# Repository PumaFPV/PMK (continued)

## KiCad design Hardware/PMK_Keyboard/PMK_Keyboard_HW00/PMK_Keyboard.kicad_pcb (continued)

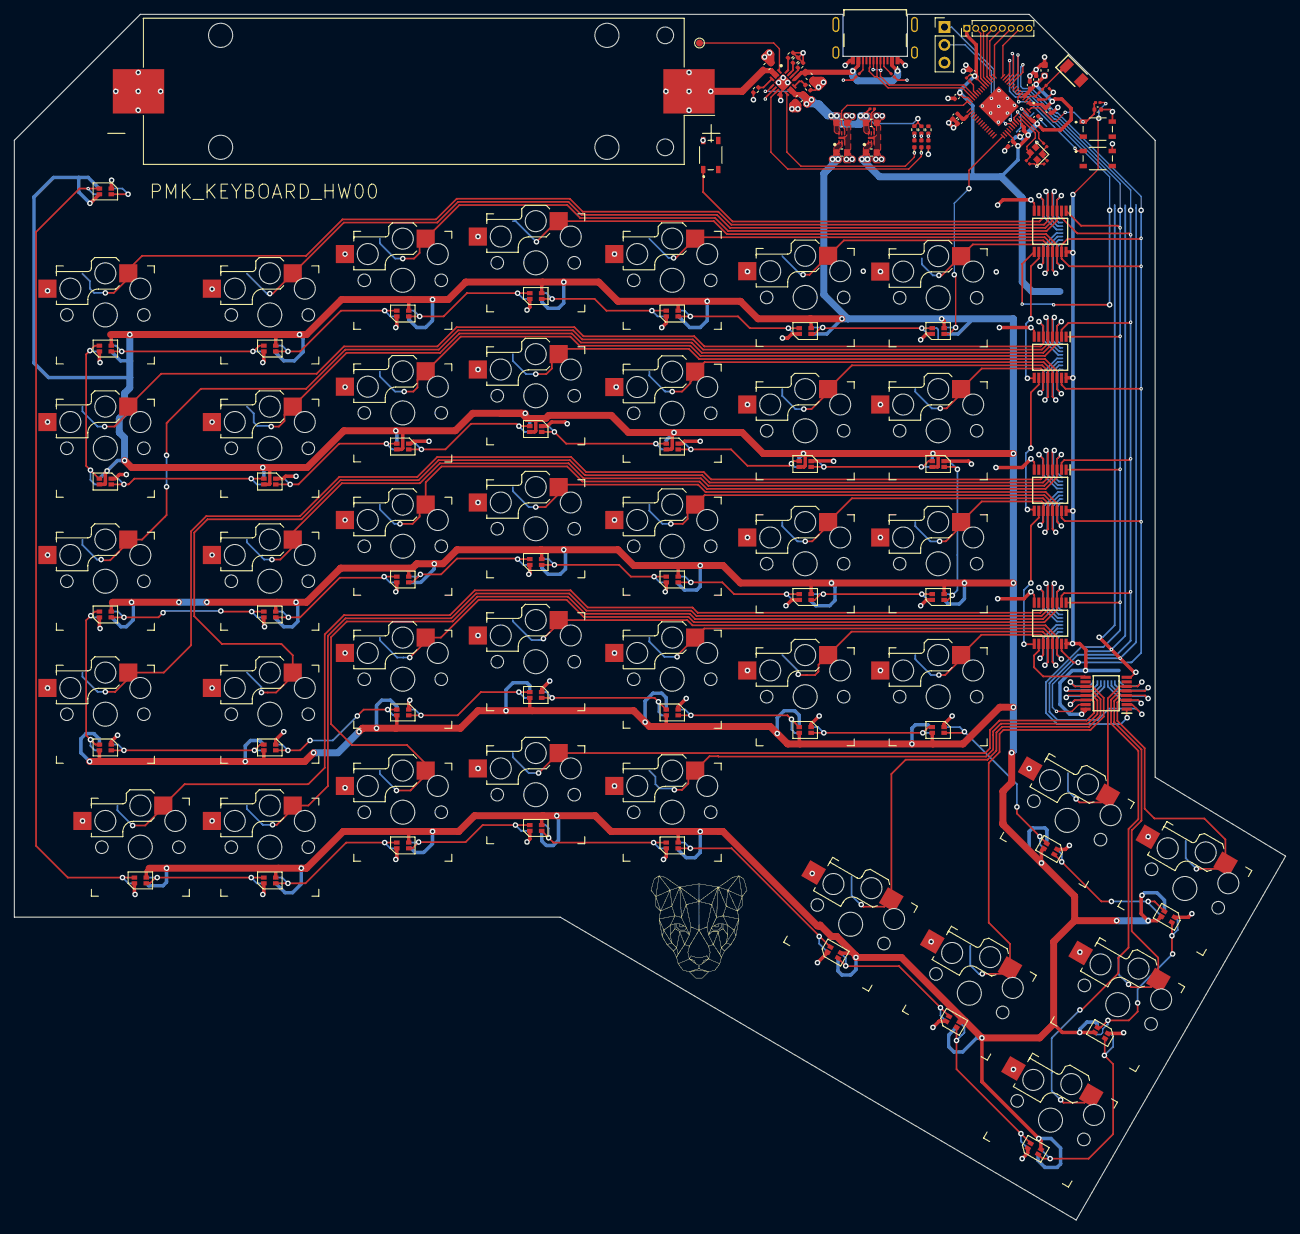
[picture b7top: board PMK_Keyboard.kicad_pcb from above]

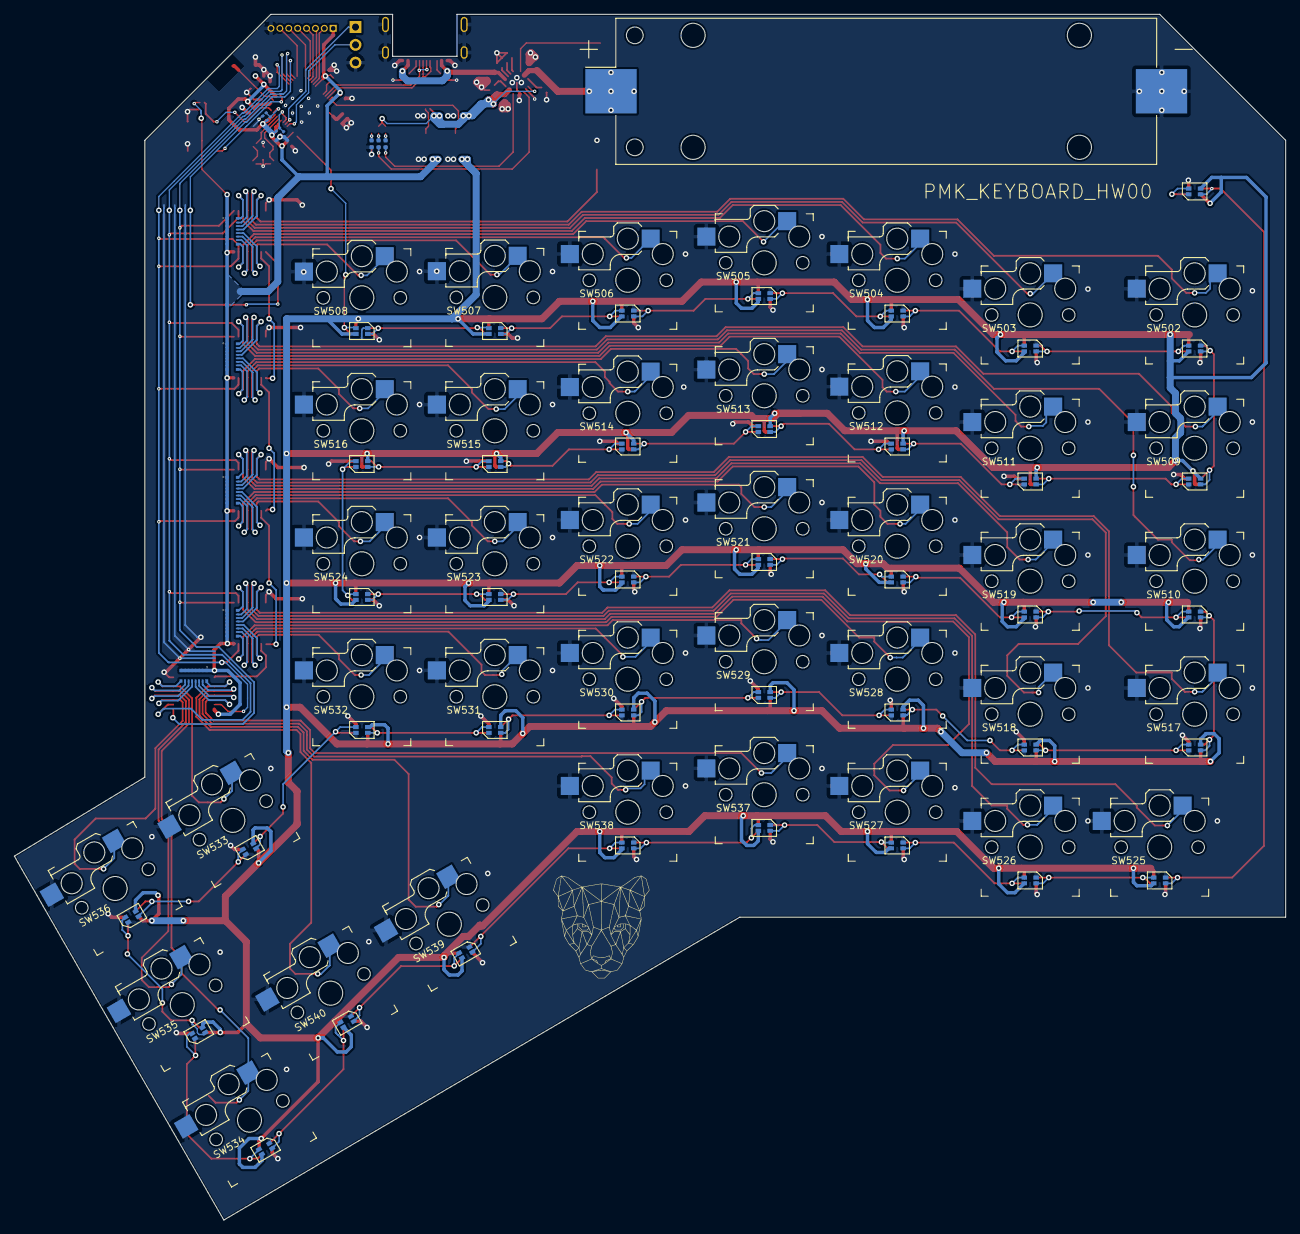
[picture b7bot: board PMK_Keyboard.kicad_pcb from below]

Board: 2 copper layers, 181.6 x 172.3 mm, 148 parts (9 on the bottom side), 130 nets.

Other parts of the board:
TP201: TestPoint; TestPoint_Pad_D1.0mm

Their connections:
/200- 1S_Charger/BATTERY_TEMP: TP201.1; also elsewhere on the board

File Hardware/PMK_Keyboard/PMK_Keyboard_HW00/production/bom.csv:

Designator,Footprint,Quantity,Value,LCSC Part #
ANT401,ANTC3216X140N,1,2450AT18A100E,
BT101,BatteryHolder_Keystone_1042_1x18650_DUALSIDE,1,Battery_Cell,
"C201, C203",0603,2,4u7,
C202,0603,1,1u,
"C301, C302, C303, C304",0603,4,2u2,
"C401, C402",0201,2,15p,
"C403, C404, C405, C408, C411, C412, C414, C415, C416",0402,9,100n,
"C406, C407",0201,2,C,
C409,0603,1,10u,
"C410, C413",0402,2,1u,
"D201, D202, D401",0402,3,LED,
"D601, D602, D603, D604, D605, D606, D607, D608, D609, D610, D611, D612, D613, D614, D615, D616, D617, D618, D619, D620, D621, D622, D623, D624, D625, D626, D627, D628, D629, D630, D631, D632, D633, D634, D635, D636, D637, D638, D639, D640",YF923_2020_WS2812_LED_DUALSIDE,40,YF923_2020_WS2812_LED,
J101,USB4510031A,1,USB4510-03-1-A,
J401,PinHeader_1x08_P1.27mm_Vertical,1,Conn_01x08_Female,
J402,PinHeader_1x03_P2.54mm_Vertical,1,Conn_01x03_Socket,
L401,0201,1,L,
"R101, R102",0201,2,5.1k,
R201,0402,1,0,
R202,0402,1,36k5,
R203,0402,1,590,
R204,0402,1,1k1,
"R205, R206",0402,2,1k5,
R207,0402,1,100k,
R301,0201,1,0k,
R401,0201,1,0,
R402,0402,1,2k,
"R403, R404",0201,2,10k,
"R405, R406, R407, R408",0201,4,nu,
"RN501, RN502, RN503, RN504, RN505",EXB2HV_1,5,EXB-2HV103JV,
"S401, S402",SKRPABE010,2,SKRPABE010,
SW501,SKRPABE010,1,SW_Push,
"SW502, SW503, SW504, SW505, SW506, SW507, SW508, SW509, SW510, SW511, SW512, SW513, SW514, SW515, SW516, SW517, SW518, SW519, SW520, SW521, SW522, SW523, SW524, SW525, SW526, SW527, SW528, SW529, SW530, SW531, SW532, SW533, SW534, SW535, SW536, SW537, SW538, SW539, SW540",Kailh_socket_PG1350_reversible,39,SW_Push,
TP201,TestPoint_Pad_D1.0mm,1,TestPoint,
U201,QFN50P300X300X100-17N-D,1,BQ24075RGTR,
"U301, U302",SON40P120X120X60-7N-D,2,MIC5528-3.3YMT-T5,
U401,QFN40P700X700X90-57N-D,1,ESP32-S2FH4,
"U501, U502, U503, U504, U505",SOP65P640X120-16N,5,SN74HC165PWR,
Y601,Crystal_SMD_2016-4Pin_2.0x1.6mm,1,Crystal_GND24_Small,

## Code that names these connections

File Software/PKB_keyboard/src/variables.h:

#ifndef variables_h
#define variables_h

#include "config.h"

#include "SPI.h"
#include "USB.h"
#include "USBHIDKeyboard.h"
#include "WiFi.h"
#include "esp_now.h"
#include "FastLED.h"
#include "pmk.h"


//--------------------------------------------------Define--------------------------------------------------
//----------Global values
#define MIRCOS2SECONDS 1000000

//----------GPI

//----------GPO

//----------ADC

//----------PWM

//----------LED
#define UPDATES_PER_SECOND 30


//----------Peripherals
//---UART
//HardwareSerial debug = HardwareSerial(0);


//---I2C

//---SPI
#define SR_SPI_BUS 1 //Which SPI bus to use for this SPI object
#define SR_MISO 3
#define SR_CLK 7
#define SR_CE 9
#define SR_PL 5

static const int srSpiClk = 10000000; // 1MHz


//--------------------------------------------------Initialize libraries--------------------------------------------------
SPIClass * srSpi = NULL;
SPISettings settingsA(srSpiClk, MSBFIRST, SPI_MODE0);

USBHIDKeyboard Keyboard;

CRGB leds[NUM_LEDS];
CRGBPalette16 currentPalette;
TBlendType    currentBlending;

esp_now_peer_info_t peerInfo;

telemetryStruct telemetryPacket;
keyboardStruct keyboardPacket;
keyboardStruct previousKeyboardPacket;
keyboardStruct releaseKeyboardPacket;

//--------------------------------------------------Structs--------------------------------------------------
struct Func
{
  uint16_t counter;
  unsigned long beginTime;
  unsigned long startCounterTime;
  unsigned long endTime;
  unsigned long duration;
  const    long interval;
  uint8_t frequency;
  unsigned long inBetweenTime;
};

Func ledTask = {0, 0, 0, 0, 0, 10000, 0, 0};
Func srTask = {0, 0, 0, 0, 0, 1000, 0, 0};
Func espnowTask = {0, 0, 0, 0, 0, 1000, 0, 0};
Func uartTask = {0, 0, 0, 0, 0, 20000, 0, 0};

struct NoDelay
{
  unsigned long interval;  //in ms
  unsigned long previousMillis;
  unsigned long currentMillis;
};

NoDelay pulsarNoDelay = {6, 0, 0};

struct Debounce
{
  uint8_t state;
  uint8_t lastState;
  unsigned long lastDebounceTime;
  unsigned long debounceDelay;
  uint8_t reading;
};

//--------------------------------------------------Variables--------------------------------------------------
//84:F7:03:F0:EF:72
uint8_t dongleAddress[] = {0x58, 0xCF, 0x79, 0xA3, 0x98, 0xC2};

extern CRGBPalette16 myRedWhiteBluePalette;
extern const TProgmemPalette16 myRedWhiteBluePalette_p PROGMEM;

uint8_t receivedData[16];
String success;

uint8_t spiPacket[5] = {0x00, 0x00, 0x00, 0x00, 0x00};
uint8_t numberOfPressedKeys = 0;

uint8_t ledNumber = 0;
uint8_t ledBrightness = 50;

uint8_t layerID = 0;



#endif

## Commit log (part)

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2022-11-10 POC of dongle + keyboard
    dongle appears as Serial + Keyboard + MSC
    When keyboard is powered it sends its data
2022-11-10 Added firmware MSC update
2022-11-10 dont press keyboard if 0
2022-11-11 added 2nd keyboard address
2022-11-11 readme test
2022-11-14 added packets struct
2022-11-14 added device ID to packets
2022-11-15 trying littlefs
2022-11-23 quick update
2022-11-25 unifying rf packet
2022-12-01 some work done on espNowHandle
2022-12-02 bon euh ça marche pas
2022-12-05 it builds
2022-12-05 keyboard led functions and responds to macaddress command
2022-12-05 need to add setDongleMACAddress
2022-12-06 set dongle mac address wip
2022-12-18 Added a glimpse of pmk configurator
2022-12-20 Added keyboard layout
2022-12-20 yeah, schematic started
2022-12-20 project update
2022-12-20 Initiated layout
2022-12-20 Added some sort of layout
2022-12-20 firstlayouttest
2022-12-21 trying some layout scale
2022-12-22 updated layout
2023-01-02 trying some code
2023-01-03 finally the correct pcb dimension
2023-01-04 with FN row
2023-01-05 no function row
2023-01-05 updated outline
2023-01-05 changed switch footprint
2023-01-05 quick routing test
2023-01-06 Started routing
2023-01-06 Routing in progress
2023-01-08 quick routing update
2023-01-12 quick update on software
2023-01-12 Some mecha update
2023-01-12 yay routing to switches is done
2023-01-13 Started Dongle schematic
2023-01-19 Added ESP32 to schematic
2023-01-19 Updated schematic
2023-01-22 Layout is almost done
2023-01-23 Routing ongoing
2023-01-24 Updated routing to jlc specifications
2023-01-24 Routing is almost done, just need to check quartz
2023-01-25 Routing is done
2023-01-25 Dongle routing is done
2023-01-30 Redone routing for 180mm version
2023-01-31 Started routing the pullups
2023-01-31 Keyboard routing is ongoing
2023-02-01 Added LEDs
2023-02-02 added hierachic pages
2023-02-03 Worked on hierachic page again
2023-02-06 Worked on hierachic sheet
2023-02-06 Again on hierachic sheet
2023-02-07 Schematic is done, only possible update is change of ESP pins
2023-02-07 Routing is finally updated
2023-02-08 updated routing
2023-02-08 Added the correct ref for USB C connector
2023-02-15 added battery footprint
2023-02-20 Routing is almost done
2023-02-20 added schematic for reverse polarity protection
2023-02-27 Added reverse polarity battery management
2023-03-02 removed anti reverse polarity system
2023-03-02 Routed the debug uart
2023-03-13 HW00 of keyboard is done but ugly
2023-03-14 back to software (keyboard for now)
2023-03-14 reading and computing the data from the shiftregisters
2023-03-16 Messing around with a trackball
2023-03-20 working on the software
2023-04-14 changed file architecture
2023-04-29 made a first version of the dongle casing
2023-04-30 Made a 2nd version of casing
2023-05-07 Working on software
2023-05-10 Tested the LED
2023-05-11 added pulsar led color
2023-05-12 Every key is working !!
2023-05-14 Working on the keyboard part
2023-05-14 Windows key doesnt work alone
2023-05-15 Added layers, brightness ajustement
2023-05-16 started dongle code
2023-05-16 mmh I broke pulsar
2023-05-18 fixing some of the compiling errors
2023-05-24 trying some stuff for the pulsar function
2023-05-31 Updated 3D file
2023-05-31 added step file of key layout
2023-06-04 Trying some runonce stuff
2023-06-19 working on dongle
2023-06-19 trying some layer stuff
2023-07-02 small work
2023-07-06 working on wireless implementation
2023-07-08 Updated the readme!!
2023-07-08 small mistake
2023-07-09 tiny cleanup
2023-07-25 doesnt compile...
2023-07-26 fixed compilation errors
2023-07-26 Keyboard and dongle compile fine!
2023-07-26 Wireless comm works
    big latency, some keys seem to be dead on the keyboard
2023-07-27 played with led to see power consumption
2023-07-30 Working on Json config file implementation
2023-08-01 working on configs
2023-08-02 finished power consumption measurements
2023-08-02 working on config
2023-08-14 fixed reading json
2023-08-15 Now configuring device ID via json file
2023-08-16 Config mac address works
2023-08-16 formating
2023-08-16 added packet structure to readme
2023-08-21 started support for all packets type
2023-08-21 trying some stuff on the usb
2023-08-23 started on adding all packet reading support
2023-08-23 insulting myself
2023-08-28 Started designing keycaps
2023-09-04 Added support for mouse and gamepad
2023-09-05 Added gamepad handle + some cleanup
2023-09-07 updated file structure
2023-09-08 Added firmware MSC
2023-09-08 FirmwareMSC added, "fixed latency"
2023-09-12 gamepad and mouse tested and are working
2023-09-16 looking for inspiration for the configurator
2023-09-16 updated mecha
2023-10-02 started 3D mouse CAD
2023-11-21 Added FCS and WCS devices
2023-11-21 doing some cleanup
2023-11-22 cleaned FCS and WCS
2023-12-10 added mecha for deej
2023-12-27 removed old naming
2023-12-27 moved dongle pcb to HW00
2024-01-21 moved folders
2024-02-08 started keyboard HW01
2024-02-09 Working on schematic
2024-02-12 working on routing
2024-02-12 led routing
2024-02-12 Need to route Shift registers
2024-02-13 Routing still going on
2024-02-13 a bit of routing
2024-02-14 Need to add some silkscreenthen done!
2024-02-14 commit before trying kicad 8.0 rc2
2024-02-15 added mounting holes + fix in ref des
2024-02-19 removed those stupids backups
2024-02-20 updated PSoM holes
2024-02-25 working on file system...
2024-02-26 Updated psom placement
2024-02-28 Saved produced gerbers
2024-02-28 working on fatfs integration
2024-03-06 added stencil holder
2024-03-10 updated keyboard code for HW01
2024-03-11 USB MSC works!!
2024-03-12 integrating tinyUSB
2024-03-15 USB mouse and keyboard works
2024-03-15 implemented new hid method to pmk.h
2024-03-15 quick fix for previous commit
2024-03-15 quick backup before messing up file system read
2024-03-15 LeftKB wireless communication works!!!
2024-03-18 figuring out config file doesnt quite works
2024-03-19 QoL improvement
2024-03-29 working on mecha
2024-04-03 Updating key reading function
2024-04-03 fixed reading button 0 bug
2024-04-04 Fixed led number, added rotary encoder pins
2024-04-05 Added WiFi power option
2024-04-05 started work on power measurements
2024-04-06 PMK messages are recevied by dongle but no HID output...
2024-04-06 Communication from keyboard to dongle works
2024-04-06 It works great
2024-04-06 Added SPIFlash to deps
2024-04-07 Keyboard report works
2024-04-08 just playing with keyboard leds before reassigning keys
2024-04-08 Config updated, IT WORKS!!
2024-04-09 Rotary encoder reading added
    Still need HW fix to had capa ton rotary encoder...
2024-04-09 updated lib deps
2024-04-09 fixed 5555555555 bug
2024-04-09 quick cleanup
2024-04-09 started implementing 2for1 feature
2024-04-10 tried something with rotary encoder + more power on wifi
2024-04-10 small cleanup + export case stl
2024-04-10 tried something for the 2for1 feature
2024-04-10 Not 2for1, more like 8for1 8-)
2024-04-10 6KRO error added
2024-04-11 Added layer management
2024-04-15 Reading key layer config from json (first step!)
2024-04-16 Config key layout works via json
2024-04-16 Mouse and keyboard work!!
2024-04-17 updated mouse code + small fix
2024-04-17 Added Consumer control and gamepad
2024-04-18 Consummer control works, brightness control is weird....
2024-04-18 added debounce to consummer control
2024-04-22 added keyboard knob + quick dongle cleanup
2024-04-22 consider rotary encoder fix done...
2024-04-22 updated knurling on knob
2024-04-22 updated tolerance
2024-04-22 rotary for left keyboard
2024-04-22 Handle keyboard on packet recevie, shorter latency
2024-04-22 removed handle from loop
2024-04-22 updated gamepad device code
2024-04-22 gamepad 8 for 1
2024-04-24 started adding 3 dongle compatibility
2024-04-26 added keycaps...
2024-04-30 added uart command to retrieve info from dongle or set custom layer
2024-04-30 added restart feature
2024-05-02 Give a use to those rotary encoders
2024-05-03 added mouse buttons to keyboard
2024-05-03 made new layout
2024-05-04 fixed a few uart commands
2024-05-15 added uart commands to keyboard
2024-05-15 ok back to normal
2024-05-17 Added manual deviceID setup
2024-05-20 added config for deviceID
2024-05-20 Added mouse dpi config
2024-05-20 saved dongle address to eeprom
2024-05-20 cleanup code
2024-05-20 added device sample code
2024-05-21 deej implementation done!
2024-05-22 working on implementing magellan
2024-05-24 started adding support for 3D mouse
2024-05-26 quick clean
2024-05-26 3d mouse is starting to work
2024-05-29 minor corrections
2024-06-02 Added spacemouse device
2024-06-07 touched the mecha
2024-06-07 started keyboard_02
2024-06-08 working on schematic 02
2024-06-08 Updated README for spacemouse
2024-06-08 added module connector
2024-06-10 Schematic 02 done
2024-06-12 updated key switch to kailh v2
2024-06-15 routing almost done
2024-06-15 PMK_Keyboard_02 is done
2024-06-16 started space mouse
2024-06-16 added production files for spacemouse_00
2024-06-26 added BOM for PMK_Keyboard_02
2024-06-26 fixed typo on silkscreen, no new rev for this fix
2024-06-27 Added iBom for spacemouse
2024-06-27 Added support for keyboard HW02
2024-06-27 HW02 fix
2024-06-27 Added keyboard support for cirque trackpad
2024-06-27 started adding space mouse
2024-07-01 working on spacemouse support
2024-07-01 fixed typo in platformio.ini
2024-07-02 working on side modules
2024-07-03 spacemouse driver should work
2024-07-03 trying to bring up the space mouse
2024-07-04 added RTOS counter for uartTask
2024-07-05 Added spacemouse support
2024-07-06 working on mecha!
2024-07-10 casing v0 done!
2024-07-12 mecha v0 done
2024-07-15 added right top plate stl
2024-07-16 trying some configurator things
2024-07-23 fixed spi settings
2024-07-25 did some cleaning
2024-07-27 did some side module cleaning
2024-07-27 added info uart command
2024-07-27 updated the test configurator file
2024-07-30 moved right plate location
2024-07-30 moved html configurator
2024-07-30 added debug options
2024-08-02 Added pmk_dongle_s2 with proper VID PID
2024-08-06 it aint clean but it does work! fixed format
2024-08-08 started cleaning up
2024-08-08 added foam
2024-08-09 doesnt compile
2024-08-09 1.0.0 dongle commit
2024-08-09 Release 1.0.0
2024-08-12 fixed the -_ in the layout
2024-08-12 added command to change esp now bit rate
2024-08-16 added spacemouse_01
    fixed the 2 unrouted paths
2024-08-16 Routing PMK_Dongle_S2_HW01
    fixed the previous issues + shortened by 3mm
2024-08-18 working on PMK-dongle_S3 schematic
2024-08-18 started routing dongle_s3_00
2024-08-20 started PMK_Dongle_C_nRF
2024-08-20 started routing PMK_Dongle_C_NRF_00
2024-08-28 updated firmware rev
2024-08-28 updated hw03 todo
2024-08-29 looking for the input lag
2024-09-05 made a bigger psom hole
2024-09-07 working on battery telemetry
2024-09-08 Added battery reading
2024-09-08 finally made a real layout
2024-09-28 Trying to reduce input lag + fixed force layer bug
2024-09-30 typo
2024-10-02 updated input lag reseach
2024-10-17 added mouse shell prototype
2024-10-17 removed old layout
2024-10-21 added top viewe layout
2024-10-21 Added todo with VIK standard connector
2024-10-23 updated layer change HID code
2024-10-23 have i just resolved the input lag issue?
2024-10-25 added screenshot from debounce
2024-10-25 updated refresh rate to 200Hz for debounce fix
2024-10-25 added battery command and debug toggle option
2024-10-25 added another debug toggle + fixed the config file
2024-11-25 started pmk_03
2024-11-30 finalised 3D mouse knob
2025-01-09 Added configurator POC
2025-06-24 fixed layout and keyboard debug
    and added command for setting channel
2025-06-24 finished SpaceMouse_01
2025-06-30 fixed hole size for order
2025-10-01 init PMK_Mouse
2025-10-01 started schematic
2025-10-05 touched scroll wheel
2025-12-31 Fixed onDataRecv for new esp now api
2026-01-01 turn off leds when no keys have been pressed for 5 min
2026-03-16 Release 1.0.2
    Updated serial interface to use simpleCLI.
    Turn off keyboard LED after specified amount of time.
2026-03-16 Release 1.0.2 fix
2026-03-17 adding midi on top of deej for volume control
2026-03-17 working on midi intergration
2026-03-18 added midi support
2026-03-18 PMK_deek is empty
